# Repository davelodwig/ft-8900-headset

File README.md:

# ft-8900-headset
Headset adapter for the Yaseu FT-8800 / FT-8900

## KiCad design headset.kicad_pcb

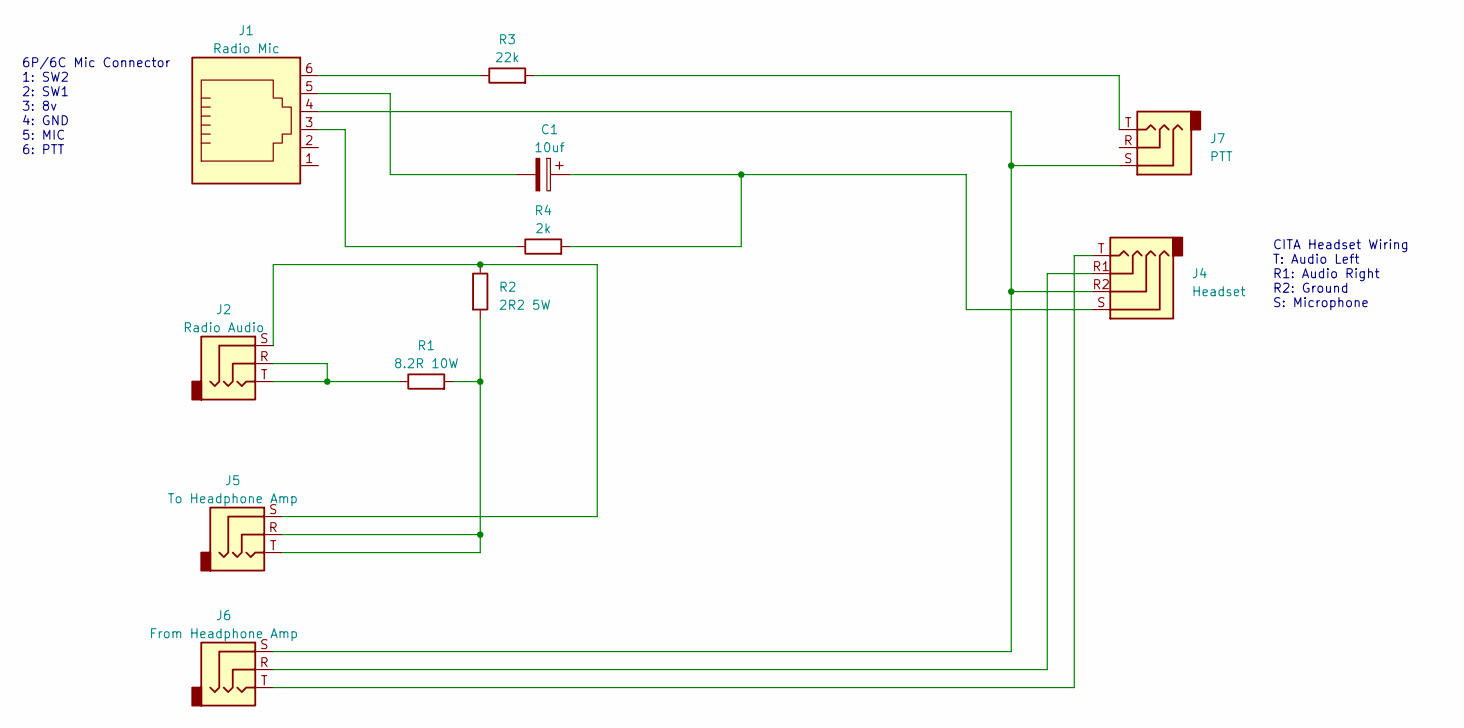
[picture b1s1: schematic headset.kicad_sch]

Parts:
C1: 10uf; CP_Radial_D5.0mm_P2.00mm
J1: Radio Mic; RJ12_Amphenol_54601
J2: Radio Audio; Jack_3.5mm_CUI_SJ1-3523N_Horizontal
J4: Headset; Jack_3.5mm_PJ320E_Horizontal
J5: To Headphone Amp; Jack_3.5mm_CUI_SJ1-3523N_Horizontal
J6: From Headphone Amp; Jack_3.5mm_CUI_SJ1-3523N_Horizontal
J7: PTT; Jack_3.5mm_CUI_SJ1-3523N_Horizontal
R1: 8.2R 10W; R_Axial_DIN0204_L3.6mm_D1.6mm_P5.08mm_Horizontal
R2: 2R2 5W; R_Axial_DIN0204_L3.6mm_D1.6mm_P5.08mm_Horizontal
R3: 22k; R_Axial_DIN0204_L3.6mm_D1.6mm_P5.08mm_Horizontal
R4: 2k; R_Axial_DIN0204_L3.6mm_D1.6mm_P5.08mm_Horizontal

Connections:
unnamed: C1.1, J4.S, R4.2
unnamed: C1.2, J1.5
unnamed: J1.3, R4.1
unnamed: J1.4, J4.R2, J6.S, J7.S
unnamed: J1.6, R3.1
unnamed: J2.R, J2.T, R1.1
unnamed: J2.S, J5.S, R2.1
unnamed: J4.R1, J6.R
unnamed: J4.T, J6.T
unnamed: J5.R, J5.T, R1.2, R2.2
unnamed: J7.T, R3.2

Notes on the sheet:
CITA Headset Wiring T: Audio Left R1: Audio Right R2: Ground S: Microphone
6P/6C Mic Connector 1: SW2 2: SW1 3: 8v 4: GND 5: MIC 6: PTT

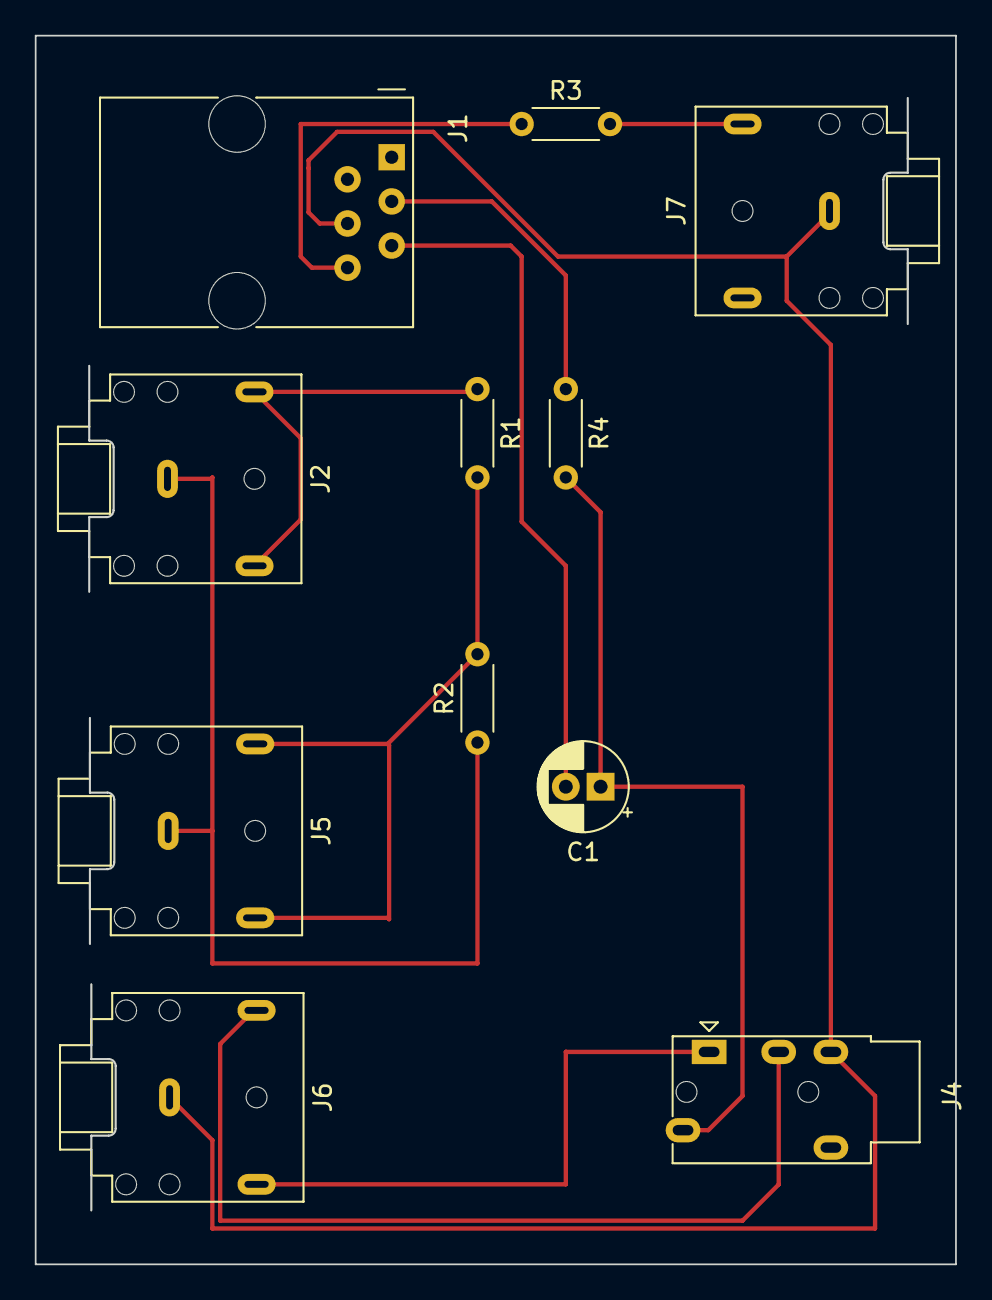
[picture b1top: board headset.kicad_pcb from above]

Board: 2 copper layers, 52.9 x 70.6 mm, 11 parts (0 on the bottom side), 11 nets.

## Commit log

2023-03-17 gitignore update
2023-03-17 intial commit of circuit designs
